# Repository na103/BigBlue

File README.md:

# HARDITAL Zorro Big Blue

Reverse engineering of **Hardital Zorro Big Blue**, an Italian Amiga expansion produced in the late 1980s.

## What it was
The Zorro Big Blue was an external metal cabinet (roughly 46×37×15 cm) that gave Amiga 500 owners — and Amiga 1000 owners, possibly with some modifications — the expansion capabilities normally reserved for the Amiga 2000. It connected to the host through the 86-pin side expansion connector and provided a backplane with **three Zorro II slots and three ISA slots**, plus drive bays for 3.5" and 5.25" floppies, a hard disk bay, a cooling fan, and a 40W power supply.
The ISA slots could not host PC cards directly from the Amiga side: they were usable only in combination with an x86 bridgeboard installed in the system, and the ISA cards remained accessible only to the PC side of that setup. The name "Big Blue" refers to this PC-compatibility angle ("Big Blue" being IBM's nickname).</br>
At the time of [The Games Machine](Misc/TGM.jpeg) review ( by Carlo Santagostino November 1989), the system retailed for 180,000 Italian Lire for the backplane plus 150,000 Lire for the chassis, a competitive alternative to buying a full Amiga 2000.
</br></br>
</br>
</br>

</br></br>

## What this repository contains

Reverse engineering of the programmable logic on the system, distributed across two interconnected boards:

**Board A** — host interface and transceiver steering between the host Amiga and the backplane</br></br>
  
**Board B** — Zorro II backplane carrying the three slots, with bus arbitration, address decoding, and Amiga collision detection</br></br>

The two `PAL16L8` chips (steering on Board A, collision detection on Board B) were fully extracted using [DuPAL](https://github.com/DuPAL-PAL-DUmper) and reimplemented as documented `GAL16V8` replacements with annotated CUPL sources. Minor differences between the original PALs and their GAL replacements — tri-state behavior, product term limits, polarity conventions — are noted in the source files.

The `PAL16R8` used for Zorro bus arbitration (on Board B) was **not** fully decoded: DuPAL doesn't reliably handle registered outputs (the state space requires specific clock sequences that brute-force extraction can't fully explore). Its equations were instead reconstructed by comparing the chip's response to the [Peeper](https://github.com/DuPAL-PAL-DUmper/DuPAL_Peeper) with the schematics of the early Amiga 2000 revision, which uses a functionally similar arbitration block.

The repository includes:

- Reconstructed KiCad schematics of both boards
- Annotated CUPL sources for the GAL replacements, with inline documentation of design decisions

## A note on the board condition

The unit examined for this reverse engineering shows several signs that suggest it is **not a final production board** but rather a prototype or a pre-production revision:

- **Multiple bodge wires**: several PCB traces have been cut and rerouted with flying wires, both on the signal layer and on what should be solid ground areas
- **Missing components**: the AC termination resistor network on seven bus lines (A22, A23, D11-D15) was desoldered at some point and never reinstalled; its corresponding capacitors remain in place but are electrically inert without the resistor
- **Hardwired override**: SLVOUT (an output of the collision detection PAL) is shorted directly to GND, in direct conflict with the PAL's output driver — a configuration that disables the original collision-handling protocol between the Amiga-side and ISA-side logic
- **Inconsistencies in the PAL logic** point in the same direction: the arbitration PAL has the BG0 output programmed as permanently inactive, making slot 0 non-mastering by design, and the steering PAL on Board A actively drives an AOE (Address Output Enable) signal whose corresponding pin on the package is not connected to anything on the PCB — meaning the PAL programming carries logic for a function the board doesn't physically use

Whether these are factory choices in a cost-reduced design, leftover modifications from a pre-production prototype, or later field hacks by a previous owner is impossible to say with certainty without comparing against other surviving units. The reverse engineering documented here describes **the board as found**, with notes where the original design intent can be reasonably inferred.

## Hardware validation

The reverse-engineered logic has been validated on real hardware in its period-correct configuration: **Amiga 500 + Kickstart 1.3 + Zorro II memory expansion**. In this setup the system boots and operates, with all three Zorro II slots functional for passive cards (RAM, I/O).

A few limitations emerged during testing and are worth documenting:

- **Slot 0 does not support bus mastering.** This is by design in the original PAL programming, not a fault. DMA-capable cards (SCSI controllers, accelerators with onboard DMA) must be installed in slot 1 or 2.
- **DMA SCSI controllers work with difficulty.** The Commodore A2091 operates in the configuration above but with occasional read errors during sustained transfers. PIO-only SCSI controllers would likely be a better match for this board.
- **Kickstart 2.0+** has not been validated with DMA SCSI cards. Period-correct Kickstart 1.3 is the recommended configuration.
- **Bus signal quality** is at the edge of specification, consistent with the cost-reduced design of the cabinet and likely contributing to the SCSI DMA errors. Marginal +5V regulation under load, clock distribution through the buffered bus, and 30-year-old connector contacts all contribute.

In short: the Big Blue is fully functional for its intended use case (light expansion of an A500 with period-correct software), and the limitations are inherent to its 1989 design philosophy rather than to faults in the hardware.

## Credits and sources

- Period reviews from *Commodore Computer Club* and *The Games Machine* magazines (1989)
- The [DuPAL]([https://github.com/AlessandroDeLuca/dupal](https://github.com/DuPAL-PAL-DUmper)) project for the combinational PAL extraction
- Early Amiga 2000 schematics, for cross-reference on the arbitration logic

## Thanks
A big thank you to Carlo Santagostino for providing HARDITAL Zorro BigBlue and historical memory

If you found this my work useful, please consider buying me a cup of coffee if you want:<br>

## License

This work is licensed under a Creative Commons Attribution 4.0 International License. See [https://creativecommons.org/licenses/by/4.0/](https://creativecommons.org/licenses/by/4.0/).

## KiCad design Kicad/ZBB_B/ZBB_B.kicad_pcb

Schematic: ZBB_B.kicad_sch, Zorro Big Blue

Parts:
C1, C2, C4, C5, C28, C29, C30, C60: 100uF; CP_Radial_D8.0mm_P3.80mm
C3, C103, C104: 100nF; C_Rect_L4.6mm_W2.0mm_P2.50mm_MKS02_FKP02
C6: 100uF 25V; CP_Radial_D8.0mm_P3.80mm
C7, C8, C9, C10, C11, C12, C13, C14, C15, C16, C17, C18, C19, C20, C21, C22, C23, C24, C25, C26, C31, C32, C33, C34, C35, C36, C37, C38, C39, C40, C41, C42, C43, C44, C45, C46, C47, C48, C49, C50, C51, C52, C53, C54, C55, C56, C57, C58, C59, C61, C62, C63, C64, C65, C66, C67, C68, C69, C70, C71, C72, C73, C74, C75, C76, C77, C78, C79, C80, C81, C82, C83, C84, C85, C86, C87, C88, C89, C90, C91, C92, C93, C94, C95, C96, C97, C98, C99, C100, C101, C102: 1nF; C_Rect_L4.6mm_W2.0mm_P2.50mm_MKS02_FKP02
C27: 1nFC; C_Rect_L4.6mm_W2.0mm_P2.50mm_MKS02_FKP02
CN1: 640901-3; Molex_SPOX_5267-05A_1x05_P2.50mm_Vertical; Mouser Part Number 571-640901-3
J1: EXPANSION_SLOT; PinHeader_2x52_P2.54mm_Vertical
J2, J3, J4: Zorro-II
J5, J6, J7: ISA_16_Bit_Extended; ISA 16 Bit
J8, J9, J10: ISA_8_Bit; ISA 8 Bit
JP1: SolderJumper_2_Bridged; SolderJumper-2_P1.3mm_Bridged_RoundedPad1.0x1.5mm
R1, R2: 1K; R_Axial_DIN0207_L6.3mm_D2.5mm_P7.62mm_Horizontal
RN1, RN2: 10K; R_Array_SIP8
RN3, RN6, RN8, RN13, RN16, RN17, RN18: 1K; R_Array_SIP6
RN4: 1K; R_Array_SIP8
RN5, RN7, RN9, RN10, RN11, RN12, RN14, RN15: 1K; R_Array_SIP10
U1, U2: ATF16V8Bxx-xxPU; DIP-20_W7.62mm
U3: 74LS32; DIP-14_W7.62mm

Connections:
/5VP: C1.1, C2.1, C3.1, C4.1, C5.1, C6.1, C28.1, C29.1, C30.1, C60.1, C103.1, C104.1, CN1.2, J1.5, J1.6, J2.5, J2.6, J3.5, J3.6, J4.5, J4.6, J5.31, J6.31, J7.31, J8.5, J8.57, J9.5, J9.57, J10.5, J10.57, R1.1, R2.1, RN1.1 (common), RN2.1 (common), RN13.1 (common), RN18.1 (common), U1.20 (V_{CC}), U2.20 (V_{CC}), U3.14 (VCC)
/7Mhz: J1.91, J2.92, J3.92, J4.92, U1.1 (I)
/+12VP: CN1.4, J1.9, J2.10, J3.10, J4.10, J8.17, J9.17, J10.17
/-5VP: CN1.5, J1.7, J2.8, J3.8, J4.8
/-12VP: CN1.3, J1.19, J2.20, J3.20, J4.20, J8.13, J9.13, J10.13
/A1_Z: C54.1, J1.30, J2.29, J3.29, J4.29
/A2_Z: C55.1, J1.28, J2.27, J3.27, J4.27
/A3_Z: C26.1, J1.25, J2.26, J3.26, J4.26
/A4_Z: C27.1, J1.23, J2.24, J3.24, J4.24
/A5_Z: C57.1, J1.22, J2.21, J3.21, J4.21
/A6_Z: C56.1, J1.24, J2.23, J3.23, J4.23
/A7_Z: C25.1, J1.27, J2.28, J3.28, J4.28
/A8_Z: C24.1, J1.29, J2.30, J3.30, J4.30
/A9_Z: C23.1, J1.31, J2.32, J3.32, J4.32
/A10_Z: C22.1, J1.33, J2.34, J3.34, J4.34
/A11_Z: C21.1, J1.35, J2.36, J3.36, J4.36
/A12_Z: C20.1, J1.37, J2.38, J3.38, J4.38
/A13_Z: C50.1, J1.40, J2.39, J3.39, J4.39
/A14_Z: C49.1, J1.42, J2.41, J3.41, J4.41
/A15_Z: C48.1, J1.44, J2.43, J3.43, J4.43
/A16_Z: C47.1, J1.46, J2.45, J3.45, J4.45
/A17_Z: C46.1, J1.48, J2.47, J3.47, J4.47
/A18_Z: C19.1, J1.51, J2.52, J3.52, J4.52
/A19: C18.1, J1.53, J2.54, J3.54, J4.54, U2.14 (I/O)
/A20: C17.1, J1.55, J2.56, J3.56, J4.56, U2.13 (I/O)
/A21: C16.1, J1.57, J2.58, J3.58, J4.58, U2.11 (I9)
/A22: C45.1, J1.58, J2.57, J3.57, J4.57, U2.9 (I8)
/A23: C44.1, J1.60, J2.59, J3.59, J4.59, RN2.8 (R7), U2.8 (I7)
/BAS: C12.1, J1.73, J2.74, J3.74, J4.74, U2.1 (I)
/BERR: J1.45, J2.46, J3.46, J4.46
/BGACK: J1.61, J2.62, J3.62, J4.62
/BG_Z0: J1.63, J2.64, U1.12 (I/O)
/BG_Z1: J3.64, U1.14 (I/O)
/BG_Z2: J4.64, U1.15 (I/O)
/BR: J1.101, U1.19 (I/O)
/BR_Z0: J1.59, J2.60, RN1.2 (R1), U1.2 (I1)
/BR_Z1: J3.60, RN1.3 (R2), U1.5 (I4)
/BR_Z2: J4.60, RN1.4 (R3), U1.6 (I5)
/BURST: J1.93, J2.94, J3.94, J4.94, R1.2, RN1.5 (R4), U1.3 (I2), U2.16 (I/O)
/C1_B: J1.15, J2.16, J3.16, J4.16
/C3_B: J1.13, J2.14, J3.14, J4.14
/CDAC_B: J1.16, J2.15, J3.15, J4.15
/CONFIG_Z0: J1.11, J2.12, U3.3, U3.4
/CONFIG_Z1: J3.12, U3.6, U3.9
/CONFIG_Z2: J4.12, U3.8, U3.12
/COPFG: J1.12, RN3.6 (R5.2), U3.1
/ConfigOut_Z0: J2.11, RN3.3 (R2.2), U3.5
/ConfigOut_Z1: J3.11, RN3.2 (R1.2), U3.10
/ConfigOut_Z2: J4.11, RN3.5 (R4.2), U3.13
/D0_Z: C38.1, J1.76, J2.75, J3.75, J4.75
/D1_Z: C37.1, J1.78, J2.77, J3.77, J4.77
/D2_Z: C36.1, J1.80, J2.79, J3.79, J4.79
/D3_Z: C35.1, J1.82, J2.81, J3.81, J4.81
/D4_Z: C34.1, J1.84, J2.83, J3.83, J4.83
/D5_Z: C33.1, J1.85, J2.86, J3.86, J4.86
/D6_Z: C7.1, J1.83, J2.84, J3.84, J4.84
/D7_Z: C8.1, J1.81, J2.82, J3.82, J4.82
/D8_Z: C9.1, J1.79, J2.80, J3.80, J4.80
/D9_Z: C10.1, J1.77, J2.78, J3.78, J4.78
/D10_Z: C11.1, J1.75, J2.76, J3.76, J4.76
/D11_Z: C39.1, J1.72, J2.71, J3.71, J4.71
/D12_Z: C40.1, J1.70, J2.69, J3.69, J4.69
/D13_Z: C41.1, J1.68, J2.67, J3.67, J4.67
/D14_Z: C42.1, J1.66, J2.65, J3.65, J4.65
/D15_Z: C43.1, J1.64, J2.63, J3.63, J4.63
/DOE: C32.2, J1.94, J2.93, J3.93, J4.93, R2.2
/DSI: J1.97, J2.98, J3.98, J4.98
/DTACK: J1.65, J2.66, J3.66, J4.66
/E: J1.49, J2.50, J3.50, J4.50
/EINT1: J1.95, J2.96, J3.96, J4.96
/FC0_Z: C53.1, J1.32, J2.31, J3.31, J4.31
/FC1_Z: C52.1, J1.34, J2.33, J3.33, J4.33
/FC2_Z: C51.1, J1.36, J2.35, J3.35, J4.35
/FCS: J1.98, J2.97, J3.97, J4.97
/GBG: C31.1, J1.96, J2.95, J3.95, J4.95, U1.4 (I3)
/GND: C1.2, C2.2, C3.2, C4.2, C5.2, C6.2, C28.2, C29.2, C30.2, C32.1, C60.2, C103.2, C104.2, CN1.1, J1.1, J1.2, J1.3, J1.4, J1.14, J1.26, J1.38, J1.50, J1.62, J1.74, J1.86, J1.87, J1.88, J1.89, J1.90, J1.92, J1.99, J1.100, J2.1, J2.2, J2.3, J2.4, J2.13, J2.25, J2.37, J2.49, J2.61, J2.73, J2.85, J2.87, J2.88, J2.89, J2.90, J2.91, J2.99, J2.100, J3.1, J3.2, J3.3, J3.4, J3.13, J3.25, J3.37, J3.49, J3.61, J3.73, J3.85, J3.87, J3.88, J3.89, J3.90, J3.91, J3.99, J3.100, J4.1, J4.2, J4.3, J4.4, J4.13, J4.25, J4.37, J4.49, J4.61, J4.73, J4.85, J4.87, J4.88, J4.89, J4.90, J4.91, J4.99, J4.100, J5.35, J6.35, J7.35, J8.1, J8.19, J8.61, J9.1, J9.19, J9.61, J10.1, J10.19, J10.61, JP1.1 (A), RN3.1 (R1), RN4.1 (common), RN5.1 (common), RN6.1 (common), RN7.1 (common), RN8.1 (common), RN9.1 (common), RN10.1 (common), RN11.1 (common), RN12.1 (common), RN14.1 (common), RN15.1 (common), RN16.1 (common), RN17.1 (common), U1.10 (GND), U1.11 (I9), U2.10 (GND), U3.2, U3.7 (GND)
/HLT: J1.56, J2.55, J3.55, J4.55
/INT2: J1.20, J2.19, J3.19, J4.19
/INT6: J1.21, J2.22, J3.22, J4.22
/IPL0: J1.39, J2.40, J3.40, J4.40
/IPL1: J1.41, J2.42, J3.42, J4.42
/IPL2: J1.43, J2.44, J3.44, J4.44
/LDS_Z: C14.1, J1.69, J2.70, J3.70, J4.70
/NCOLLIS: J1.103, U2.12 (I/O)
/OVR: J1.18, J2.17, J3.17, J4.17, U2.15 (I/O)
/OWN: J1.8, J2.7, J3.7, J4.7
/RST: J1.54, J2.53, J3.53, J4.53
/RW_Z: C15.1, J1.67, J2.68, J3.68, J4.68
/SLAVE_Z0: J2.9, RN2.7 (R6), U2.7 (I6)
/SLAVE_Z1: J3.9, RN2.6 (R5), U2.6 (I5)
/SLAVE_Z2: J4.9, RN2.5 (R4), U2.5 (I4)
/SLVOUT: J1.104, JP1.2 (B), U2.19 (I/O)
/UDS_Z: C13.1, J1.71, J2.72, J3.72, J4.72
/VMA: J1.52, J2.51, J3.51, J4.51
/VPA: J1.47, J2.48, J3.48, J4.48
/XRDY: J1.17, J2.18, J3.18, J4.18
unnamed: C58.1, J5.36, J6.36, J7.36
unnamed: C59.1, J5.34, J6.34, J7.34
unnamed: C61.1, J5.32, J6.32, J7.32
unnamed: C62.1, J5.30, J6.30, J7.30
unnamed: C63.1, J5.28, J6.28, J7.28
unnamed: C64.1, J5.26, J6.26, J7.26
unnamed: C65.1, J5.24, J6.24, J7.24
unnamed: C66.1, J5.22, J6.22, J7.22
unnamed: C67.1, J5.16, J6.16, J7.16
unnamed: C68.1, J5.14, J6.14, J7.14
unnamed: C69.1, J5.12, J6.12, J7.12
unnamed: C70.1, J5.10, J6.10, J7.10
unnamed: C71.1, J5.8, J6.8, J7.8
unnamed: C72.1, J5.6, J6.6, J7.6
unnamed: C73.1, J5.4, J6.4, J7.4
unnamed: C74.1, J5.2, J6.2, J7.2
unnamed: C75.1, J8.62, J9.62, J10.62
unnamed: C76.1, J8.60, J9.60, J10.60
unnamed: C77.1, J8.58, J9.58, J10.58
unnamed: C78.1, J8.56, J9.56, J10.56
unnamed: C79.1, J8.54, J9.54, J10.54
unnamed: C80.1, J8.52, J9.52, J10.52
unnamed: C81.1, J8.50, J9.50, J10.50
unnamed: C82.1, J8.48, J9.48, J10.48
unnamed: C83.1, J8.46, J9.46, J10.46
unnamed: C84.1, J8.44, J9.44, J10.44
unnamed: C85.1, J8.42, J9.42, J10.42
unnamed: C86.1, J8.40, J9.40, J10.40
unnamed: C87.1, J8.38, J9.38, J10.38
unnamed: C88.1, J8.36, J9.36, J10.36
unnamed: C89.1, J8.34, J9.34, J10.34
unnamed: C90.1, J8.32, J9.32, J10.32
unnamed: C91.1, J8.30, J9.30, J10.30
unnamed: C92.1, J8.28, J9.28, J10.28
unnamed: C93.1, J8.26, J9.26, J10.26
unnamed: C94.1, J8.24, J9.24, J10.24
unnamed: C95.1, J8.18, J9.18, J10.18
unnamed: C96.1, J8.16, J9.16, J10.16
unnamed: C97.1, J8.14, J9.14, J10.14
unnamed: C98.1, J8.12, J9.12, J10.12
unnamed: C99.1, J8.10, J9.10, J10.10
unnamed: C100.1, J8.8, J9.8, J10.8
unnamed: C101.1, J8.6, J9.6, J10.6
unnamed: C102.1, J8.4, J9.4, J10.4
unnamed: J5.5, J6.5, J7.5
unnamed: J5.7, J6.7, J7.7
unnamed: J5.9, J6.9, J7.9
unnamed: J5.11, J6.11, J7.11
unnamed: J5.13, J6.13, J7.13
unnamed: J5.15, J6.15, J7.15
unnamed: J5.17, J6.17, J7.17
unnamed: J5.19, J6.19, J7.19
unnamed: J5.21, J6.21, J7.21
unnamed: J5.23, J6.23, J7.23
unnamed: J5.25, J6.25, J7.25
unnamed: J5.27, J6.27, J7.27
unnamed: J5.29, J6.29, J7.29
unnamed: J5.33, J6.33, J7.33
unnamed: J8.2, J9.2, J10.2
unnamed: J8.3, J9.3, J10.3
unnamed: J8.7, J9.7, J10.7
unnamed: J8.9, J9.9, J10.9
unnamed: J8.11, J9.11, J10.11
unnamed: J8.15, J9.15, J10.15
unnamed: J8.20, J9.20, J10.20
unnamed: J8.22, J9.22, J10.22
unnamed: J8.29, J9.29, J10.29
unnamed: J8.31, J9.31, J10.31
unnamed: J8.33, J9.33, J10.33
unnamed: J8.35, J9.35, J10.35
unnamed: J8.37, J9.37, J10.37
unnamed: J8.39, J9.39, J10.39
unnamed: J8.41, J9.41, J10.41
unnamed: J8.43, J9.43, J10.43
unnamed: J8.45, J9.45, J10.45
unnamed: J8.47, J9.47, J10.47
unnamed: J8.49, J9.49, J10.49
unnamed: J8.51, J9.51, J10.51
unnamed: J8.53, J9.53, J10.53
unnamed: J8.55, J9.55, J10.55
unnamed: J8.59, J9.59, J10.59
unnamed: RN1.6 (R5), U1.7 (I6)
unnamed: RN1.7 (R6), U1.8 (I7)
unnamed: RN1.8 (R7), U1.9 (I8)
unnamed: RN2.2 (R1), U2.2 (I1)
unnamed: RN2.3 (R2), U2.3 (I2)
unnamed: RN2.4 (R3), U2.4 (I3)
unnamed: C31.2, RN4.2 (R1)
unnamed: C33.2, RN4.3 (R2)
unnamed: C34.2, RN4.4 (R3)
unnamed: C35.2, RN4.5 (R4)
unnamed: C36.2, RN4.6 (R5)
unnamed: C37.2, RN4.7 (R6)
unnamed: C38.2, RN4.8 (R7)
unnamed: C7.2, RN5.2 (R1)
unnamed: C8.2, RN5.3 (R2)
unnamed: C9.2, RN5.4 (R3)
unnamed: C10.2, RN5.5 (R4)
unnamed: C11.2, RN5.6 (R5)
unnamed: C12.2, RN5.7 (R6)
unnamed: C13.2, RN5.8 (R7)
unnamed: C14.2, RN5.9 (R8)
unnamed: C15.2, RN5.10 (R9)
unnamed: C16.2, RN6.3 (R2)
unnamed: C17.2, RN6.4 (R3)
unnamed: C18.2, RN6.5 (R4)
unnamed: C19.2, RN6.6 (R5)
unnamed: C45.2, RN7.2 (R1)
unnamed: C44.2, RN7.3 (R2)
unnamed: C43.2, RN7.5 (R4)
unnamed: C42.2, RN7.6 (R5)
unnamed: C41.2, RN7.7 (R6)
unnamed: C40.2, RN7.8 (R7)
unnamed: C39.2, RN7.9 (R8)
unnamed: C46.2, RN8.2 (R1)
unnamed: C47.2, RN8.3 (R2)
unnamed: C48.2, RN8.4 (R3)
unnamed: C49.2, RN8.5 (R4)
unnamed: C50.2, RN8.6 (R5)
unnamed: C20.2, RN9.3 (R2)
unnamed: C21.2, RN9.4 (R3)
unnamed: C22.2, RN9.5 (R4)
unnamed: C23.2, RN9.6 (R5)
unnamed: C24.2, RN9.7 (R6)
unnamed: C25.2, RN9.8 (R7)
unnamed: C26.2, RN9.9 (R8)
unnamed: C27.2, RN9.10 (R9)
unnamed: C57.2, RN10.2 (R1)
unnamed: C56.2, RN10.3 (R2)
unnamed: C55.2, RN10.5 (R4)
unnamed: C54.2, RN10.6 (R5)
unnamed: C53.2, RN10.7 (R6)
unnamed: C52.2, RN10.8 (R7)
unnamed: C51.2, RN10.9 (R8)
unnamed: C58.2, RN11.2 (R1)
unnamed: C59.2, RN11.3 (R2)
unnamed: C61.2, RN11.4 (R3)
unnamed: C62.2, RN11.5 (R4)
unnamed: C63.2, RN11.6 (R5)
unnamed: C64.2, RN11.7 (R6)
unnamed: C65.2, RN11.8 (R7)
unnamed: C66.2, RN11.9 (R8)
unnamed: C74.2, RN12.3 (R2)
unnamed: C73.2, RN12.4 (R3)
unnamed: C72.2, RN12.5 (R4)
unnamed: C71.2, RN12.6 (R5)
unnamed: C70.2, RN12.7 (R6)
unnamed: C69.2, RN12.8 (R7)
unnamed: C68.2, RN12.9 (R8)
unnamed: C67.2, RN12.10 (R9)
unnamed: J5.20, J6.20, J7.20, RN13.2 (R1)
unnamed: J5.18, J6.18, J7.18, RN13.3 (R2)
unnamed: J5.3, J6.3, J7.3, RN13.4 (R3)
unnamed: J5.1, J6.1, J7.1, RN13.5 (R4)
unnamed: C75.2, RN14.2 (R1)
unnamed: C76.2, RN14.3 (R2)
unnamed: C77.2, RN14.4 (R3)
unnamed: C78.2, RN14.5 (R4)
unnamed: C79.2, RN14.6 (R5)
unnamed: C80.2, RN14.7 (R6)
unnamed: C81.2, RN14.8 (R7)
unnamed: C82.2, RN14.9 (R8)
unnamed: C83.2, RN14.10 (R9)
unnamed: C92.2, RN15.2 (R1)
unnamed: C91.2, RN15.3 (R2)
unnamed: C90.2, RN15.4 (R3)
unnamed: C89.2, RN15.5 (R4)
unnamed: C88.2, RN15.6 (R5)
unnamed: C87.2, RN15.7 (R6)
unnamed: C86.2, RN15.8 (R7)
unnamed: C85.2, RN15.9 (R8)
unnamed: C84.2, RN15.10 (R9)
unnamed: C97.2, RN16.2 (R1)
unnamed: C96.2, RN16.3 (R2)
unnamed: C95.2, RN16.4 (R3)
unnamed: C94.2, RN16.5 (R4)
unnamed: C93.2, RN16.6 (R5)
unnamed: C102.2, RN17.2 (R1)
unnamed: C101.2, RN17.3 (R2)
unnamed: C100.2, RN17.4 (R3)
unnamed: C99.2, RN17.5 (R4)
unnamed: C98.2, RN17.6 (R5)
unnamed: J8.27, J9.27, J10.27, RN18.2 (R1)
unnamed: J8.25, J9.25, J10.25, RN18.3 (R2)
unnamed: J8.23, J9.23, J10.23, RN18.4 (R3)
unnamed: J8.21, J9.21, J10.21, RN18.5 (R4)

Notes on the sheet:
BUS Collision logic
BUS Arbitration logic

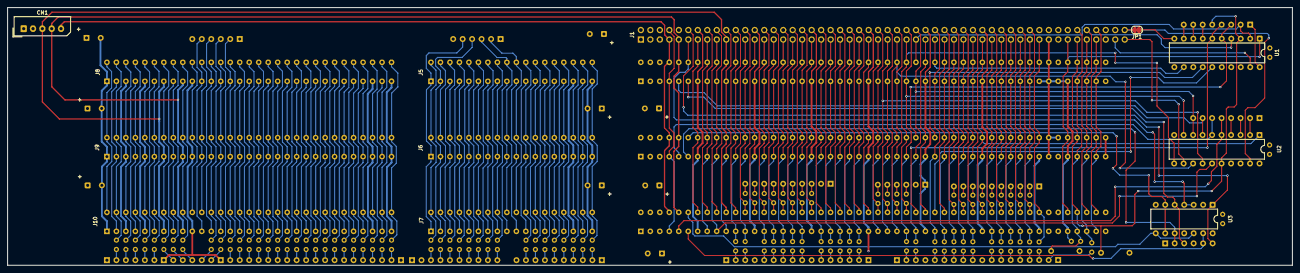
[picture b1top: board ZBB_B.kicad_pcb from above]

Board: 4 copper layers, 344.0 x 69.0 mm, 139 parts (0 on the bottom side), 282 nets.
